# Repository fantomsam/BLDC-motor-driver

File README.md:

# BLDC-motor-driver
BLDC Driver based on L6234D and MAX4373 Designed in Eagle

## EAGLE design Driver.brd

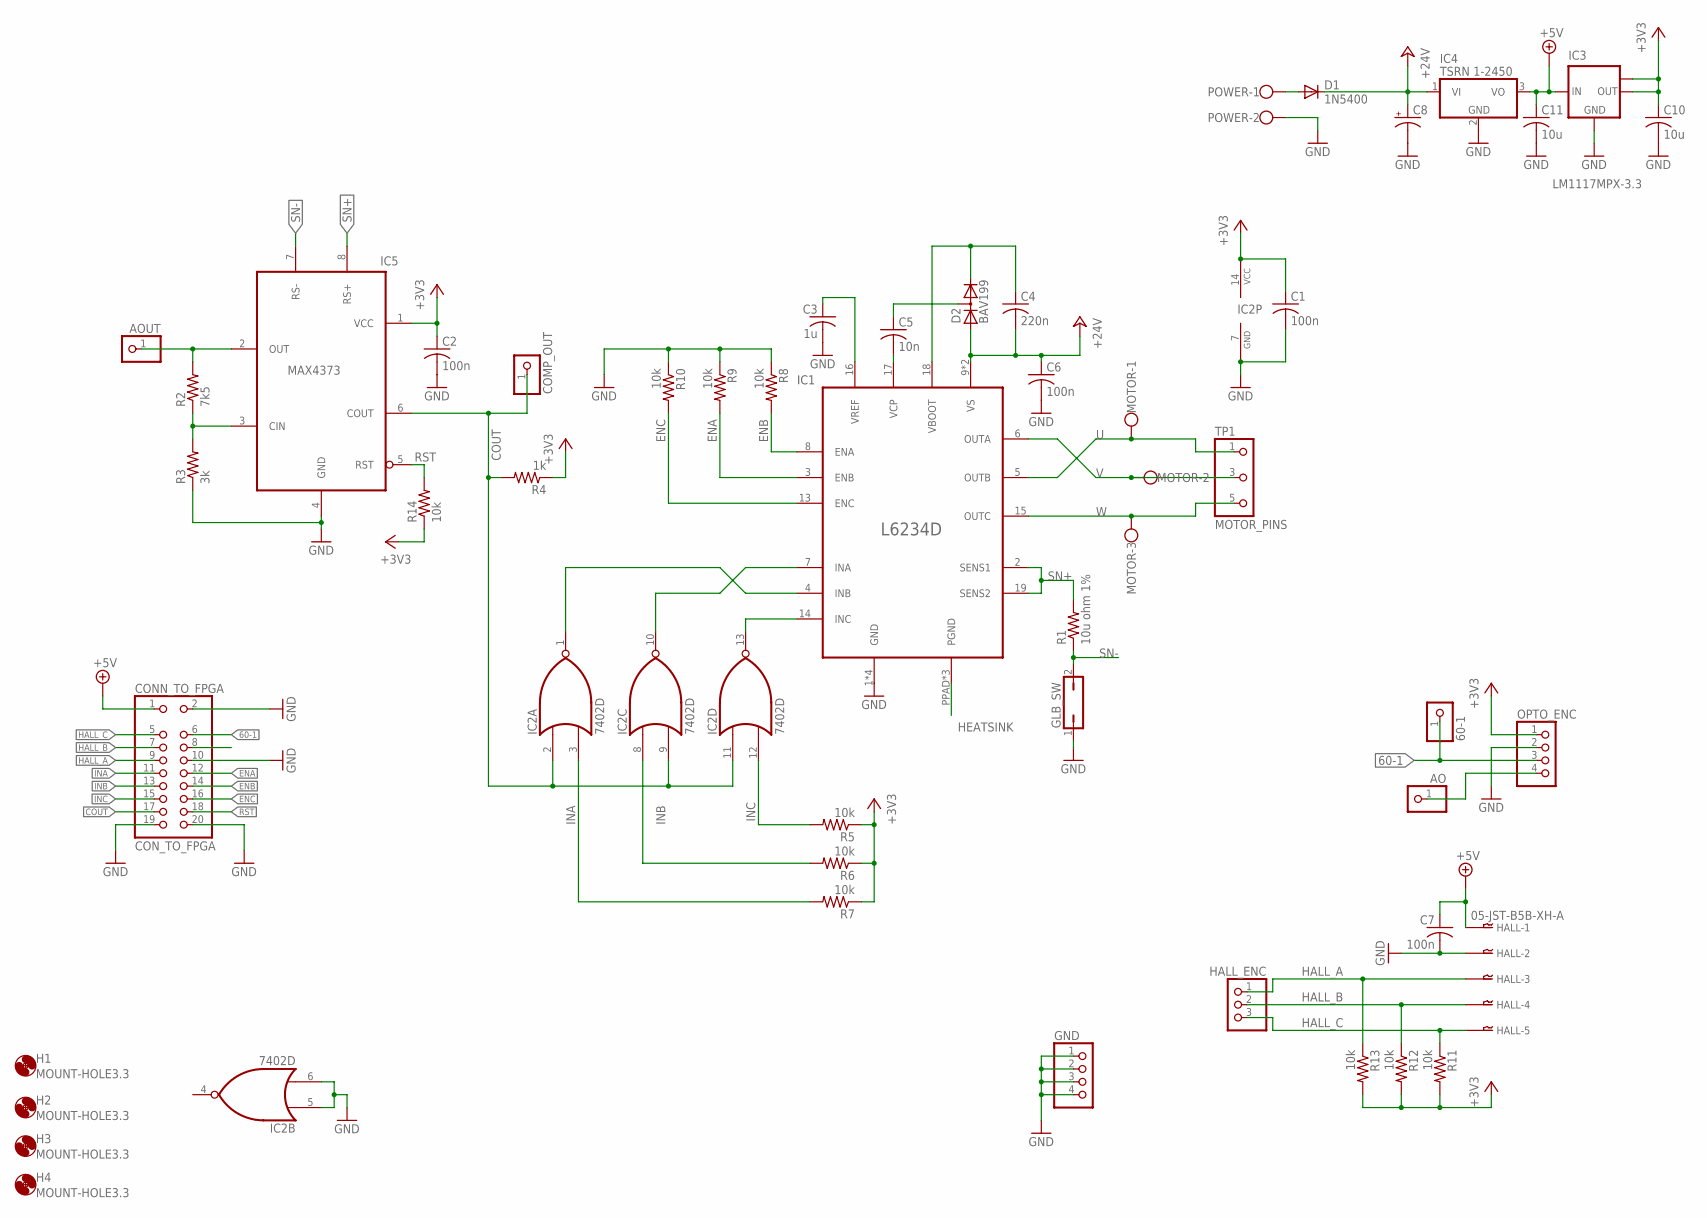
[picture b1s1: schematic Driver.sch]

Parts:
60-1: PINHD-1X1; 1X01
AO: PINHD-1X1; 1X01
AOUT: PINHD-1X1; 1X01
C1, C2, C6, C7: 100n; C0805
C3: 1u; C0805
C4: 220n; C0805
C5: 10n; C0805
C8: CPOL-USE5-13; E5-13
C10, C11: 10u; C1206K
COMP_OUT: PINHD-1X1; 1X01
CONN_TO_FPGA: CON_TO_FPGA; 2X10-2
D1: 1N5400; DO201-15
D2: BAV199; SOT23
GLB_SW: JP1Q; JP1
GND: PINHD-1X4; 1X04
H1, H2, H3, H4: MOUNT-HOLE3.3; 3,3
HALL: 05-JST-B5B-XH-A; B5B-XH
HALL_ENC: PINHD-1X3; 1X03
IC1: L6234D; POWER_SO20
IC2: 7402D; SO14
IC3: LM1117MPX-3.3; SOT223
IC4: TSRN 1-2450; TSRN-1
IC5: MAX4373; SO-8
MOTOR: W237-103
OPTO_ENC: PINHD-1X4; 1X04
POWER: W237-102
R1: 10u ohm 1%; R2512
R2: 7k5; M1206
R3: 3k; M1206
R4: 1k; M1206
R5, R6, R7, R8, R9, R10, R11, R12, R13, R14: 10k; M1206
TP1: MOTOR_PINS; PINSX3-200

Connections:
60-1: 60-1.1, CONN_TO_FPGA.6, OPTO_ENC.3
+3V3: C1.1, C2.1, C10.1, IC2.14 (VCC), IC3.2 (OUT), IC3.TAB (OUT1), IC5.1 (VCC), OPTO_ENC.1, R4.1, R5.1, R6.1, R7.1, R11.2, R12.2, R13.2, R14.1
+5V: C7.1, C11.1, CONN_TO_FPGA.1, HALL.P$1, IC3.3 (IN), IC4.3 (VO)
+24V: C4.2, C6.1, C8.+, D1.C, D2.1 (A), IC1.9 (VS), IC1.12 (VS), IC4.1 (VI)
COUT: COMP_OUT.1, CONN_TO_FPGA.17, IC2.2 (I0), IC2.9 (I1), IC2.11 (I0), IC5.6 (COUT), R4.2
ENA: CONN_TO_FPGA.12, IC1.3 (ENB), R9.2
ENB: CONN_TO_FPGA.14, IC1.8 (ENA), R8.2
ENC: CONN_TO_FPGA.16, IC1.13 (ENC), R10.2
GND: C1.2, C2.2, C3.2, C6.2, C7.2, C8.-, C10.2, C11.2, CONN_TO_FPGA.2, CONN_TO_FPGA.10, CONN_TO_FPGA.19, CONN_TO_FPGA.20, GLB_SW.1, GND.1, GND.2, GND.3, GND.4, HALL.P$2, IC1.1 (GND), IC1.10 (GND), IC1.11 (GND), IC1.20 (GND), IC2.5 (I0), IC2.6 (I1), IC2.7 (GND), IC3.1 (GND), IC4.2 (GND), IC5.4 (GND), OPTO_ENC.2, POWER.2, R3.1, R8.1, R9.1, R10.1
HALL_A: CONN_TO_FPGA.9, HALL.P$3, HALL_ENC.1, R13.1
HALL_B: CONN_TO_FPGA.7, HALL.P$4, HALL_ENC.2, R12.1
HALL_C: CONN_TO_FPGA.5, HALL.P$5, HALL_ENC.3, R11.1
HEATSINK: IC1.PPAD (PGND), IC1.PPAD1 (PGND), IC1.PPAD2 (PGND)
INA: CONN_TO_FPGA.11, IC2.3 (I1), R7.2
INB: CONN_TO_FPGA.13, IC2.8 (I0), R6.2
INC: CONN_TO_FPGA.15, IC2.12 (I1), R5.2
unnamed: D1.A, POWER.1
unnamed: IC1.14 (INC), IC2.13 (O)
unnamed: IC1.7 (INA), IC2.10 (O)
unnamed: IC1.4 (INB), IC2.1 (O)
unnamed: IC5.3 (CIN), R2.1, R3.2
unnamed: C3.1, IC1.16 (VREF)
unnamed: AOUT.1, IC5.2 (OUT), R2.2
unnamed: AO.1, OPTO_ENC.4
unnamed: C5.1, D2.3 (AC)
unnamed: C4.1, D2.2 (C), IC1.18 (VBOOT)
unnamed: C5.2, IC1.17 (VCP)
RST: CONN_TO_FPGA.18, IC5.5 (RST), R14.2
SN+: IC1.2 (SENS1), IC1.19 (SENS2), IC5.8 (RS+), R1.2
SN-: GLB_SW.2, IC5.7 (RS-), R1.1
U: IC1.5 (OUTB), MOTOR.1, TP1.1
V: IC1.6 (OUTA), MOTOR.2, TP1.3
W: IC1.15 (OUTC), MOTOR.3, TP1.5

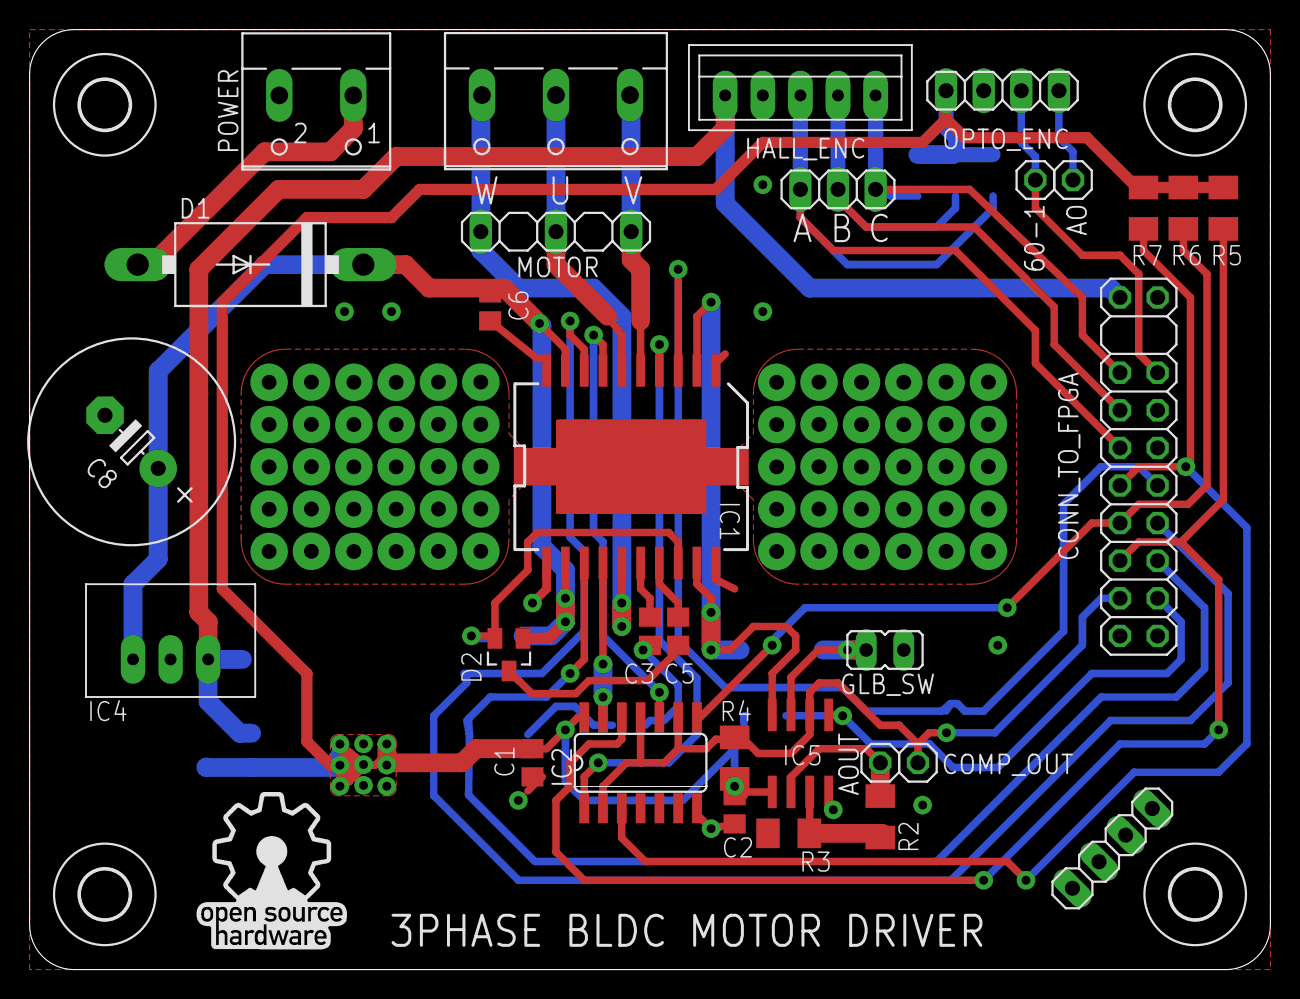
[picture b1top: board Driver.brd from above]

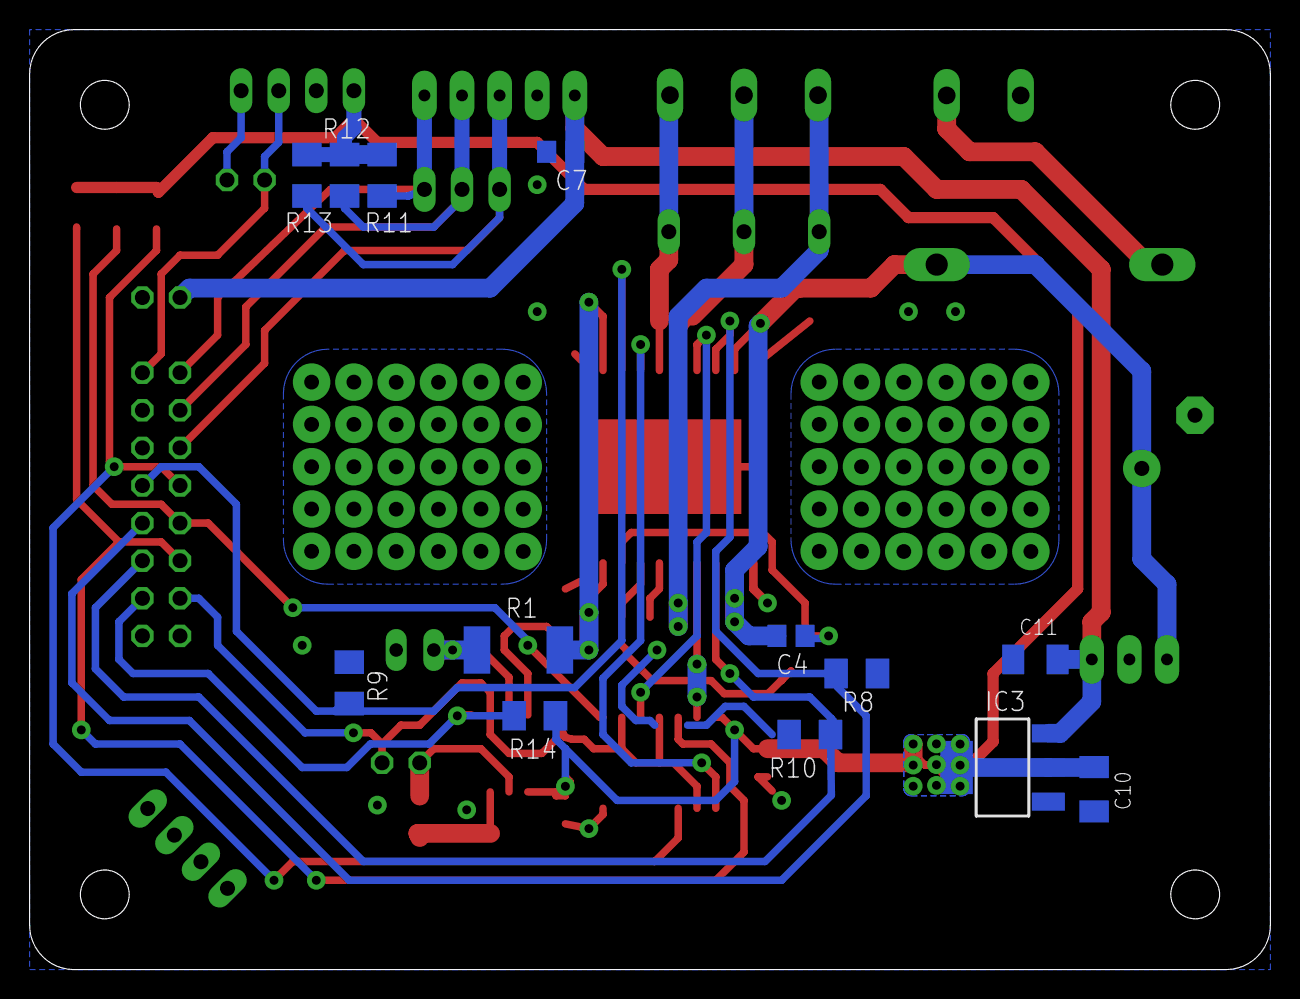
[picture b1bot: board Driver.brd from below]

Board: 2 copper layers, 83.8 x 63.5 mm, 48 parts (13 on the bottom side), 33 nets.

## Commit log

2018-05-12 Adding Project files
2018-05-20 R5..7 change layer
2018-05-29 Change on the logic of the Over Current protector
2018-05-30 add Driver sequence
2018-06-09 implement forward reverce functions
2018-06-14 Update sequence table
